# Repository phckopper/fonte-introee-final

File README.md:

# Fonte simétrica -15V-0V 0V-15V 2A
#### Fonte simétrica ajustável criada para a cadeira de Introdução à Engenharia Elétrica

## Especificações

|     Especificação     |         Ana        |        Pedro       |       Robert       |
| --------------------- | ------------------ | ------------------ | ------------------ |
| ±1.2 a ±15 VDC (Adj.) | :white_check_mark: | :white_check_mark: | :warning:          |
| 0 a ±15 VDC (Adj.)    | :heavy_minus_sign: | :white_check_mark: | :white_check_mark: |
| ±1A                   | :white_check_mark: | :warning:          | :warning:          |
| 0A a ±1A (Adj.)       | :heavy_minus_sign: | :white_check_mark: | :white_check_mark: |
| Entrada 127VAC        | :white_check_mark: | :warning:          | :warning:          |
| Entrada Bivolt        | :heavy_minus_sign: | :white_check_mark: | :white_check_mark: |
| 10% de ondulação      | :white_check_mark: | :warning:          | :warning:          |
| 3mV RMS ripple        | :heavy_minus_sign: | :white_check_mark: | :white_check_mark: |
| Output enable         | :heavy_minus_sign: | :white_check_mark: | :white_check_mark: |
| Saídas fixas (12V/5V) | :heavy_minus_sign: | :white_check_mark: | :white_check_mark: |
| Case de metal         | :heavy_minus_sign: | :white_check_mark: | :white_check_mark: |
| Pot. de 10 voltas     | :heavy_minus_sign: | :white_check_mark: | :white_check_mark: |
| Leitura digital (V/I) | :heavy_minus_sign: | :white_check_mark: | :white_check_mark: |
| Cooler com NTC        | :heavy_minus_sign: | :white_check_mark: | :white_check_mark: |
| Proteção térmica      | :heavy_minus_sign: | :white_check_mark: | :white_check_mark: |

## Requisitos

- Especificações :x:
- Diagramas esquemáticos detalhados :x:
- Memorial de cálculo, resultados de cálculos e simulações :x:
- Lista de preço dos componentes (Bill of Materials) :x:
- Datasheets em anexo :x:
- Resultados experimentais e de simulação relevantes em gráficos, tabelas e fotos. :x:

## Software utilizado

- KiCad 5.0.1

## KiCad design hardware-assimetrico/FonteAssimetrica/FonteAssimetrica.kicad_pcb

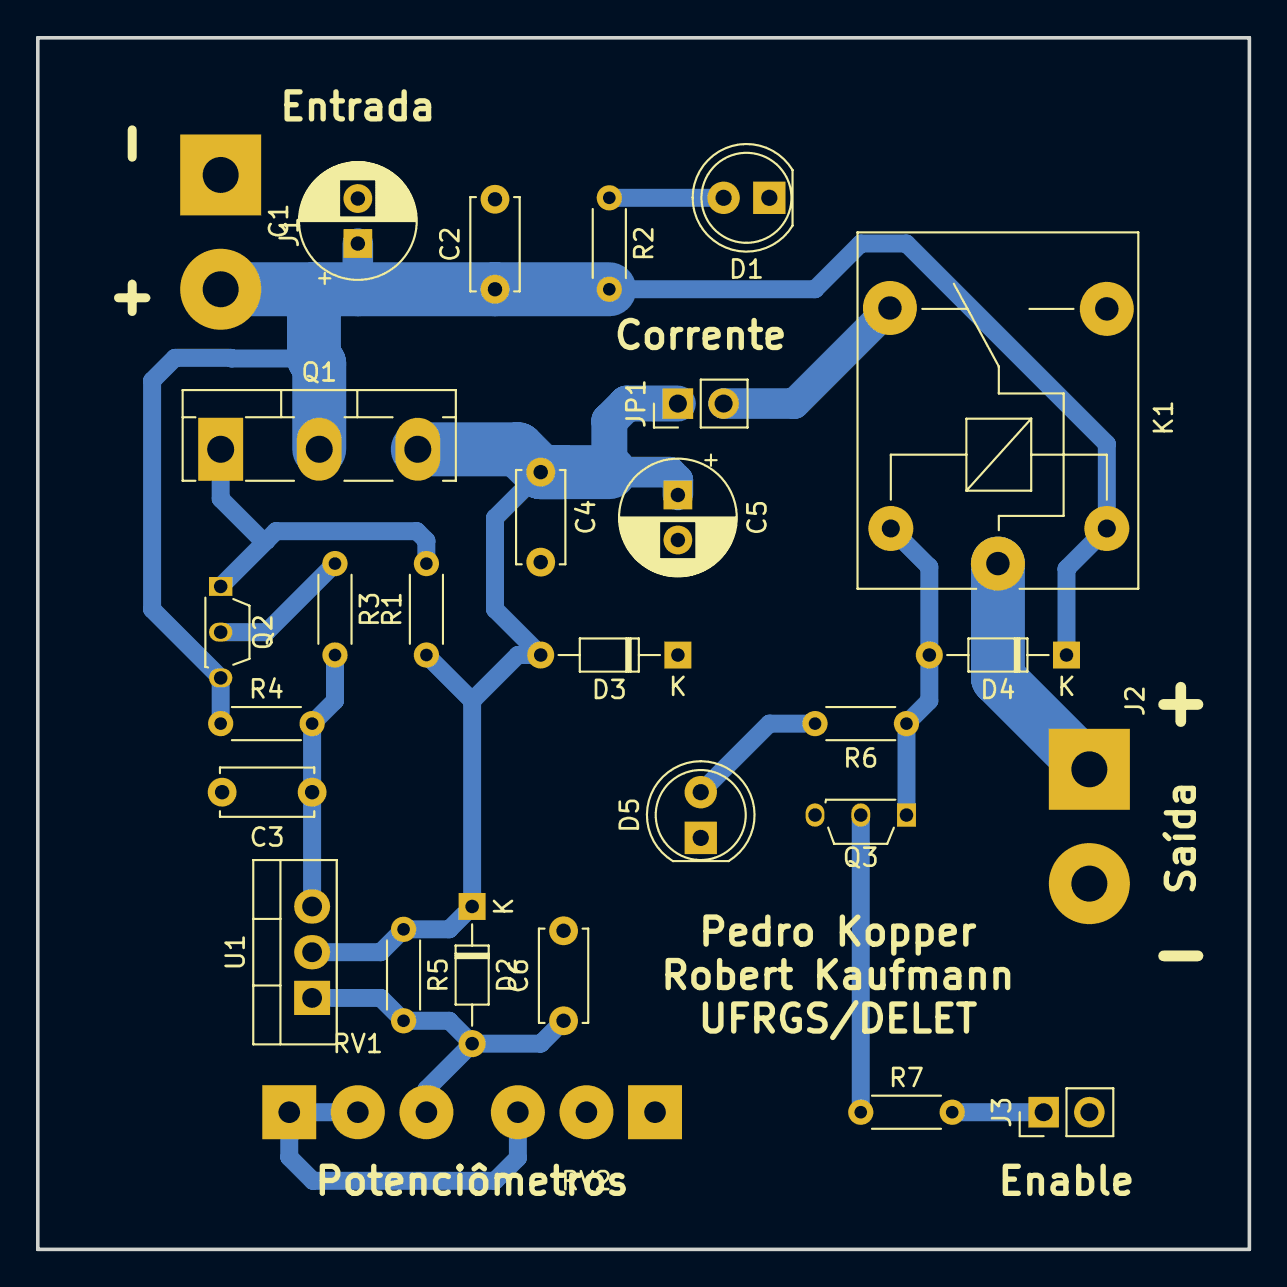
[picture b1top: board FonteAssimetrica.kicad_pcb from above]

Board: 2 copper layers, 67.3 x 67.3 mm, 29 parts (0 on the bottom side), 15 nets.

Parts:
C1, C5: 100uF; CP_Radial_D6.3mm_P2.50mm
C2: 330nF; C_Disc_D5.0mm_W2.5mm_P5.00mm
C3, C4, C6: 10uF; C_Disc_D5.0mm_W2.5mm_P5.00mm
D1: POWER; LED_D5.0mm
D2, D3, D4: D; D_DO-34_SOD68_P7.62mm_Horizontal
D5: ENABLE; LED_D5.0mm
J1: In; SolderWirePad_1x02_P7.62mm_Drill2mm
J2: Vout; SolderWirePad_1x02_P7.62mm_Drill2mm
J3: ENABLE; PinHeader_1x02_P2.54mm_Vertical
JP1: CORRENTE; PinHeader_1x02_P2.54mm_Vertical
K1: SANYOU_SRD_Form_C; Relay_SPDT_SANYOU_SRD_Series_Form_C
Q1: TIP3055; TO-218-3_Vertical
Q2: BC327; TO-92S_Wide
Q3: BC337; TO-92S_Wide
R1: 470; R_Axial_DIN0204_L3.6mm_D1.6mm_P5.08mm_Horizontal
R2, R6: 1k5; R_Axial_DIN0204_L3.6mm_D1.6mm_P5.08mm_Horizontal
R3, R7: 4k7; R_Axial_DIN0204_L3.6mm_D1.6mm_P5.08mm_Horizontal
R4: 22; R_Axial_DIN0204_L3.6mm_D1.6mm_P5.08mm_Horizontal
R5: 330; R_Axial_DIN0204_L3.6mm_D1.6mm_P5.08mm_Horizontal
RV1: 220; SolderWirePad_1x03_P3.81mm_Drill1.2mm
RV2: 5k; SolderWirePad_1x03_P3.81mm_Drill1.2mm
U1: LM317; TO-220-3_Vertical

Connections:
GND: C1.2, C2.2, C3.2, C4.2, C5.2, C6.2, D1.1, D3.1, D5.1, J1.1, J2.2, J3.2, Q3.3, RV2.1, RV2.2
unnamed: C3.1, R3.2, R4.2, U1.3
unnamed: C6.1, D2.2, R5.2, RV1.3, U1.1
unnamed: D1.2, R2.1
unnamed: D4.2, K1.5, Q3.1, R6.1
unnamed: D5.2, R6.2
unnamed: J3.1, R7.2
unnamed: JP1.2, K1.4
unnamed: Q1.1, Q2.1, R1.2
unnamed: Q2.2, R3.1
unnamed: Q3.2, R7.1
unnamed: RV1.1, RV1.2, RV2.3
VDC: C1.1, C2.1, D4.1, J1.2, K1.2, Q1.2, Q2.3, R2.2, R4.1
Vl: J2.1, K1.1
Vout: C4.1, C5.1, D2.1, D3.2, JP1.1, Q1.3, R1.1, R5.1, U1.2

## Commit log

2019-06-15 Iniciar a tabela das especificações e passar a limpo os requerimentos do relatório
2019-06-15 Começar esboço do hardware
2019-06-15 Ratificar README e adicionar lista de softwares
2019-06-23 Simulacao no LTSpice
2019-07-04 Some changes
2019-07-05 Muita coisa
